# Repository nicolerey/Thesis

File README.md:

# Thesis
Repo for "Wireless Management of Room Power Lines" Thesis

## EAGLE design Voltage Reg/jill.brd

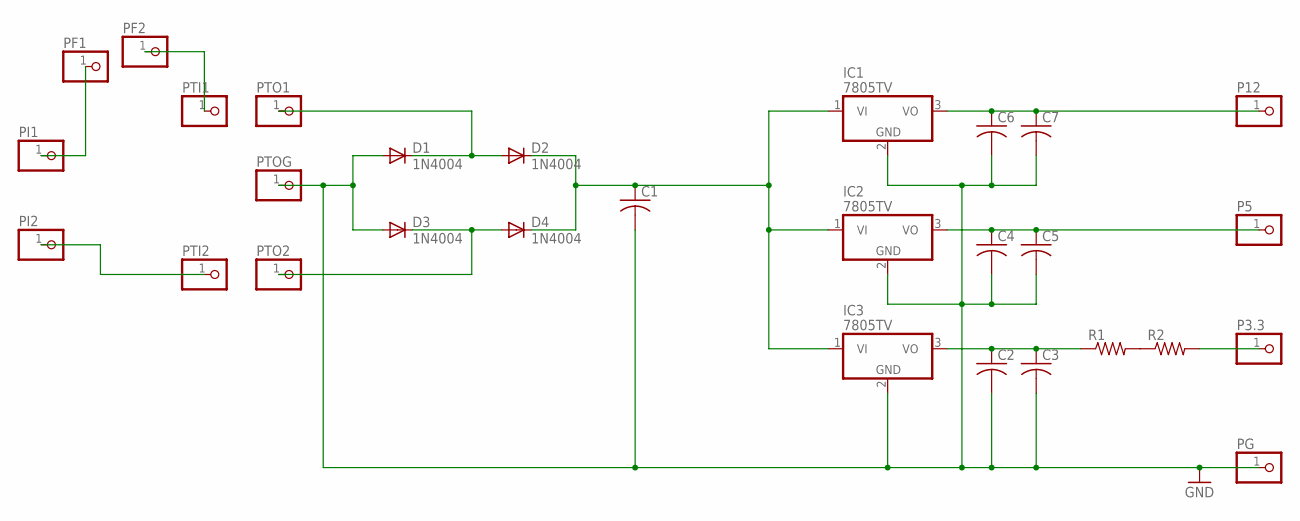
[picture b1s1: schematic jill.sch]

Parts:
C1: C-US050-075X075; C050-075X075
C2, C3, C4, C5, C6, C7: C-US025-025X050; C025-025X050
D1, D2, D3, D4: 1N4004; DO41-10
IC1, IC2, IC3: 7805TV; TO220V
P3.3, P5, P12: PINHD-1X1; 1X01
PF1, PF2: PINHD-1X1; 1X01
PG: PINHD-1X1; 1X01
PI1, PI2: PINHD-1X1; 1X01
PTI1, PTI2: PINHD-1X1; 1X01
PTO1, PTO2: PINHD-1X1; 1X01
PTOG: PINHD-1X1; 1X01
R1, R2: R-US_0207/12; 0207/12

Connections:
GND: C1.2, C2.2, C3.2, C4.2, C5.2, C6.2, C7.2, D1.A, D3.A, IC1.2 (GND), IC2.2 (GND), IC3.2 (GND), PG.1, PTOG.1
unnamed: R1.2, R2.1
unnamed: P3.3.1, R2.2
unnamed: C2.1, C3.1, IC3.3 (VO), R1.1
unnamed: C4.1, C5.1, IC2.3 (VO), P5.1
unnamed: C6.1, C7.1, IC1.3 (VO), P12.1
unnamed: C1.1, D2.C, D4.C, IC1.1 (VI), IC2.1 (VI), IC3.1 (VI)
unnamed: D1.C, D2.A, PTO1.1
unnamed: PF1.1, PI1.1
unnamed: PF2.1, PTI1.1
unnamed: PI2.1, PTI2.1
unnamed: D3.C, D4.A, PTO2.1

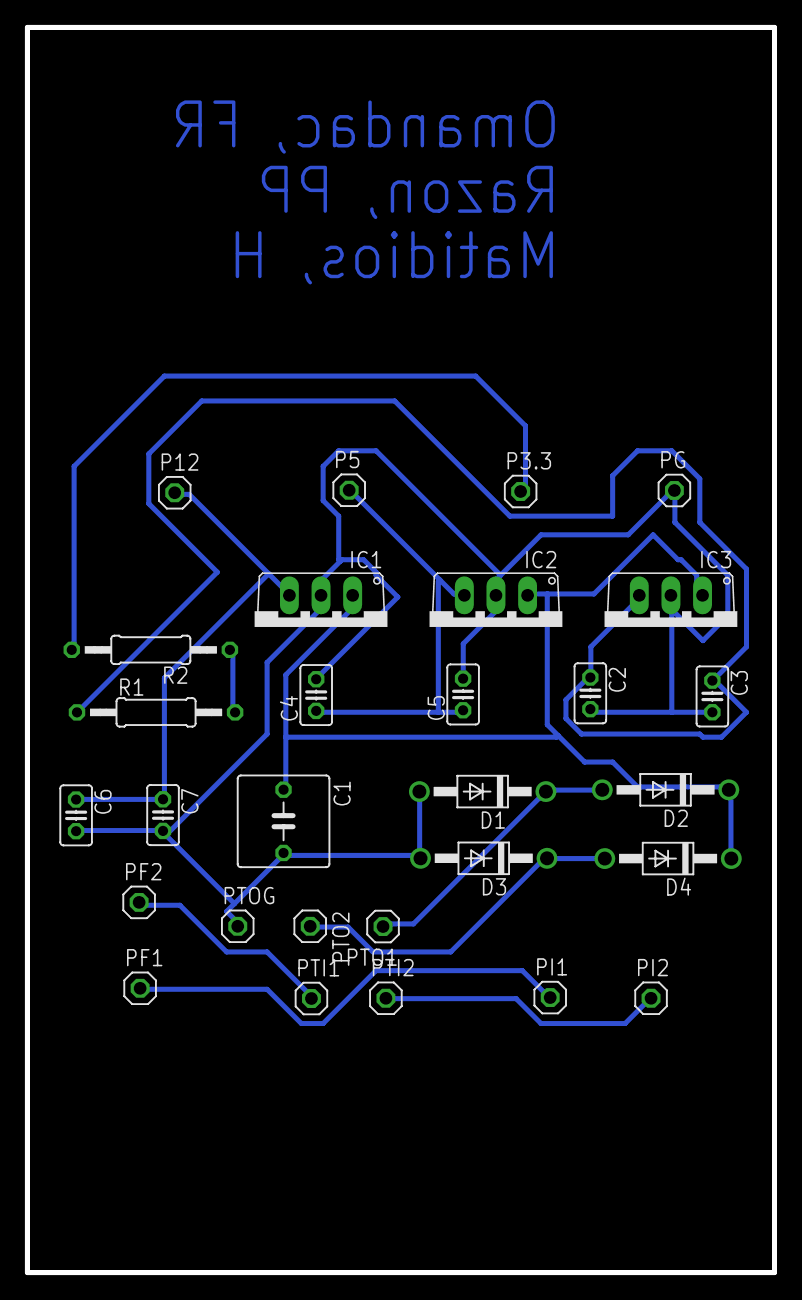
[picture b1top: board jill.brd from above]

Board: 2 copper layers, 60.0 x 100.0 mm, 29 parts (0 on the bottom side), 12 nets.

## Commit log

2015-11-08 added Arduino and Python files, codes are not final
2015-11-09 updated arduino pin config
2015-11-10 added db ERD image
2015-11-11 added test code for set and get og date & time in arduino
2015-11-12 first commit for the api
    <3
2015-11-13 organizing of API folder and uploading of v2
2015-11-14 added a postman file for the requests
2015-11-14 changed file locations
2015-11-14 added v1 of project code
2015-11-21 added voltage reg details
2015-11-21 added MYSQL-python
2015-11-22 Added dependency files for the MFC project.
    Very important files for web server requests and parsing json data
2015-12-02 GUI login
    -> First upload of GUI. It can now login.
    -> Edited documentation
2015-12-04 added multiple files
2015-12-04 puno og resource para ing code
2015-12-04 Updated include and library folder
    -> PC Compatibility issues.
2015-12-04 V3 of API.
    -> gi update kay nausab ang db. :>
2015-12-05 Continuous navigation until VIEW section
    -> still has issue in adding columns. naglisod pa. xD
    -> naglibog ko unsay idisplay sa view. if sundon ang planned UI kay
    kaduha mag request, append column.
2015-12-13 cleaned and added files
2015-12-13 changed file directories
2015-12-13 added data sql
2015-12-13 added a file
2015-12-13 edited code
2015-12-13 edited files
2015-12-13 edited file
2016-02-21 updated everything for my part
2016-03-01 added changes
2016-03-18 changed everything
2016-03-26 added and changed some
2016-03-29 added final files hopefully
2016-03-31 added tweaks
